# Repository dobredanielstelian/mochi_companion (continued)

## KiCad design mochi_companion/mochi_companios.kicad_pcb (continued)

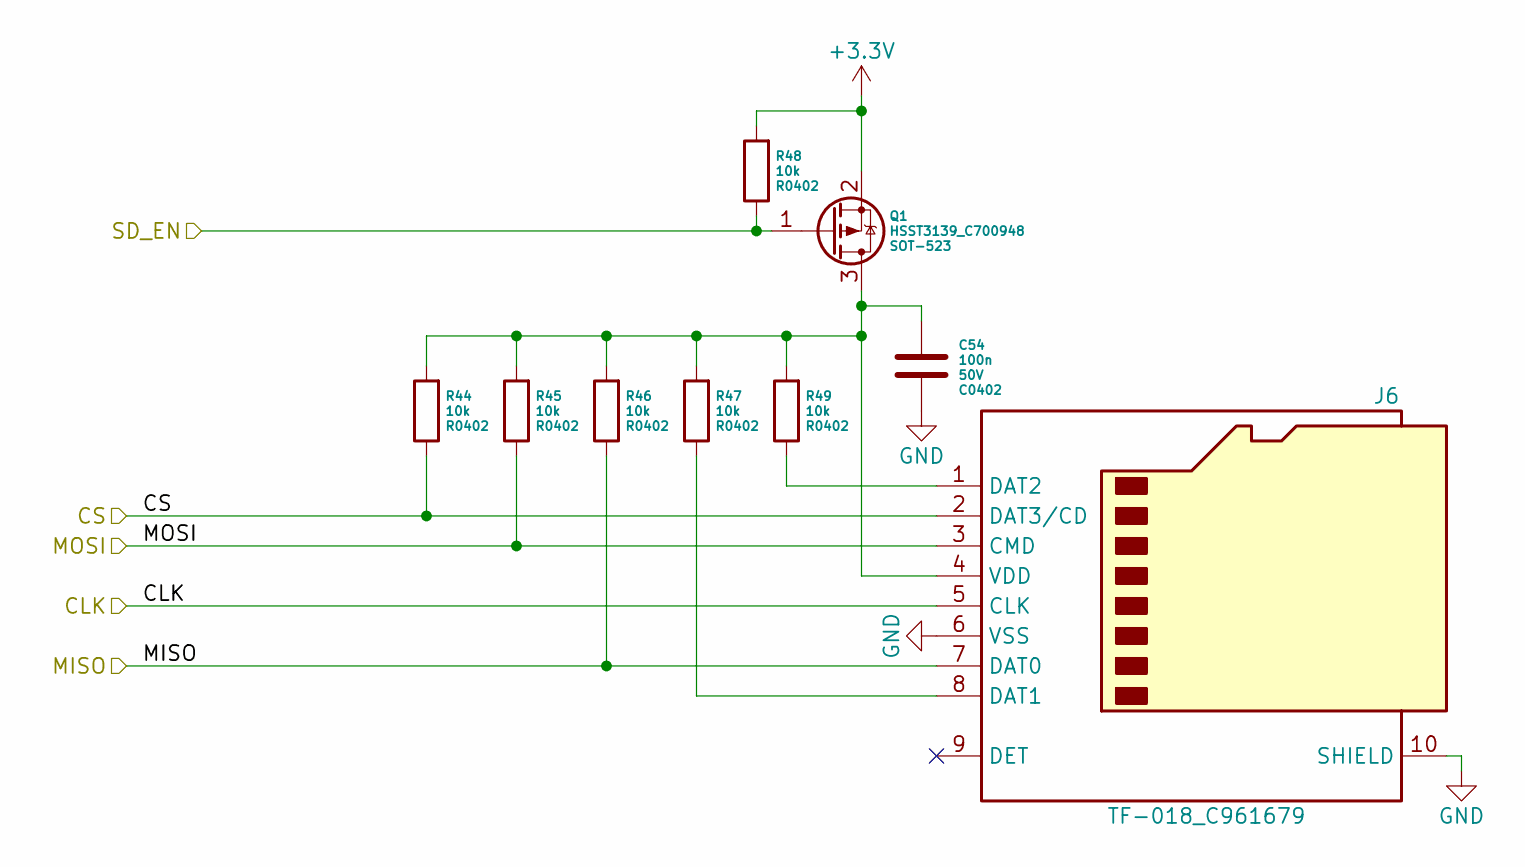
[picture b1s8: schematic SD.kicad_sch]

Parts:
C54: 100n; C_0402_1005Metric
J6: TF-018_C961679; 0101-A-B03-006_C961679
Q1: HSST3139_C700948; SOT-523
R44, R45, R46, R47, R48, R49: 10k; R_0402_1005Metric

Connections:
+3.3V: Q1.2 (S), R48.2; also elsewhere on the board
/CLK: J6.5 (CLK); also elsewhere on the board
/CS: J6.2 (DAT3/CD), R44.1; also elsewhere on the board
/MISO: J6.7 (DAT0), R46.1; also elsewhere on the board
/MOSI: J6.3 (CMD), R45.1; also elsewhere on the board
/SD_EN: Q1.1 (G), R48.1; also elsewhere on the board
GND: C54.2, J6.6 (VSS), J6.10 (SHIELD); also elsewhere on the board
unnamed: J6.8 (DAT1), R47.1
unnamed: J6.1 (DAT2), R49.1
unnamed: C54.1, J6.4 (VDD), Q1.3 (D), R44.2, R45.2, R46.2, R47.2, R49.2

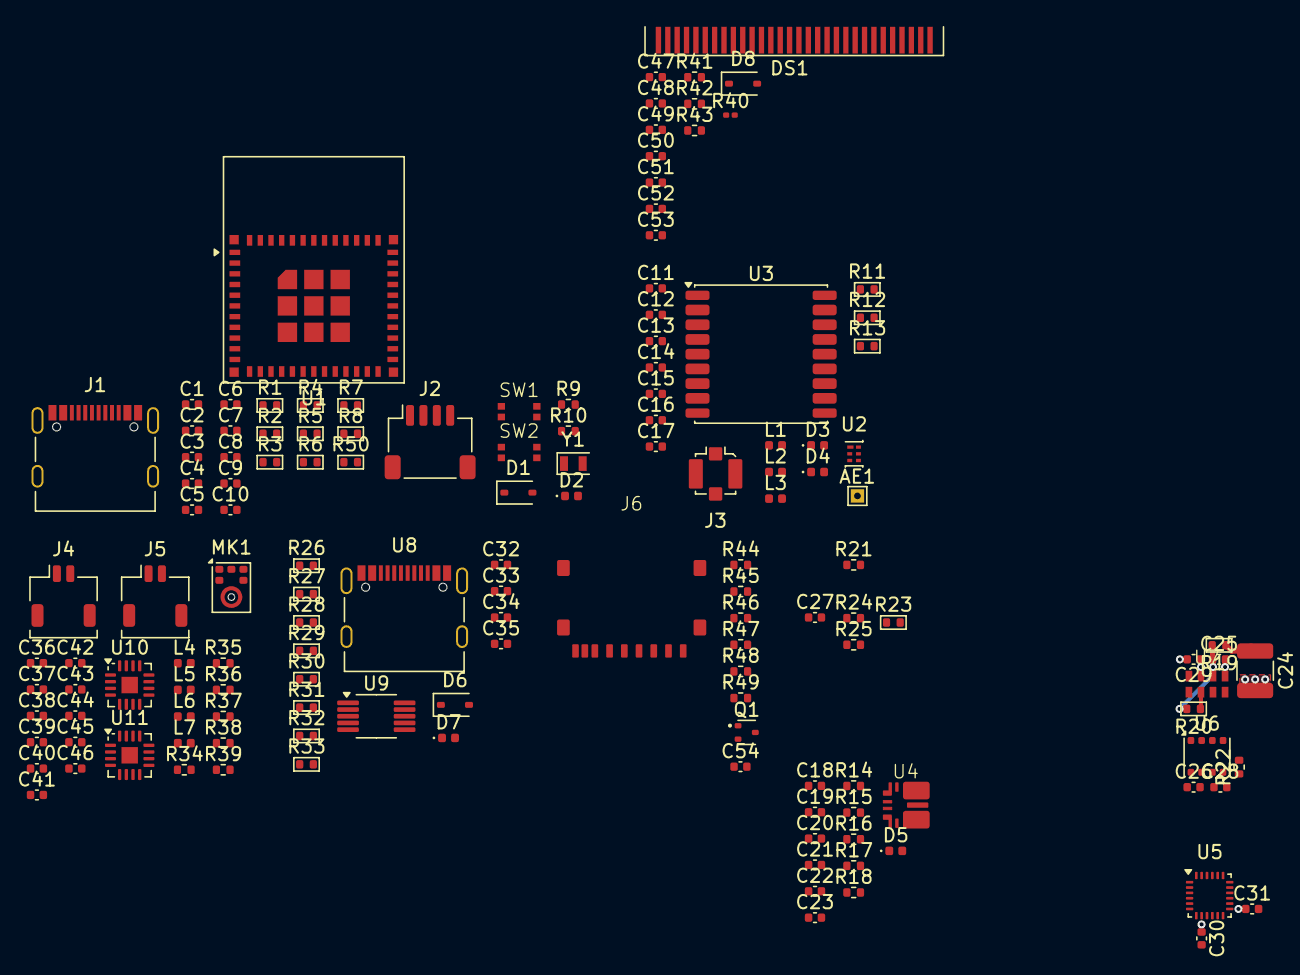
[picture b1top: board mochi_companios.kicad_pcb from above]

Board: 2 copper layers, 143 parts (0 on the bottom side), 90 nets.

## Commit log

2025-07-11 250712_0041
2025-07-12 250713_0019
